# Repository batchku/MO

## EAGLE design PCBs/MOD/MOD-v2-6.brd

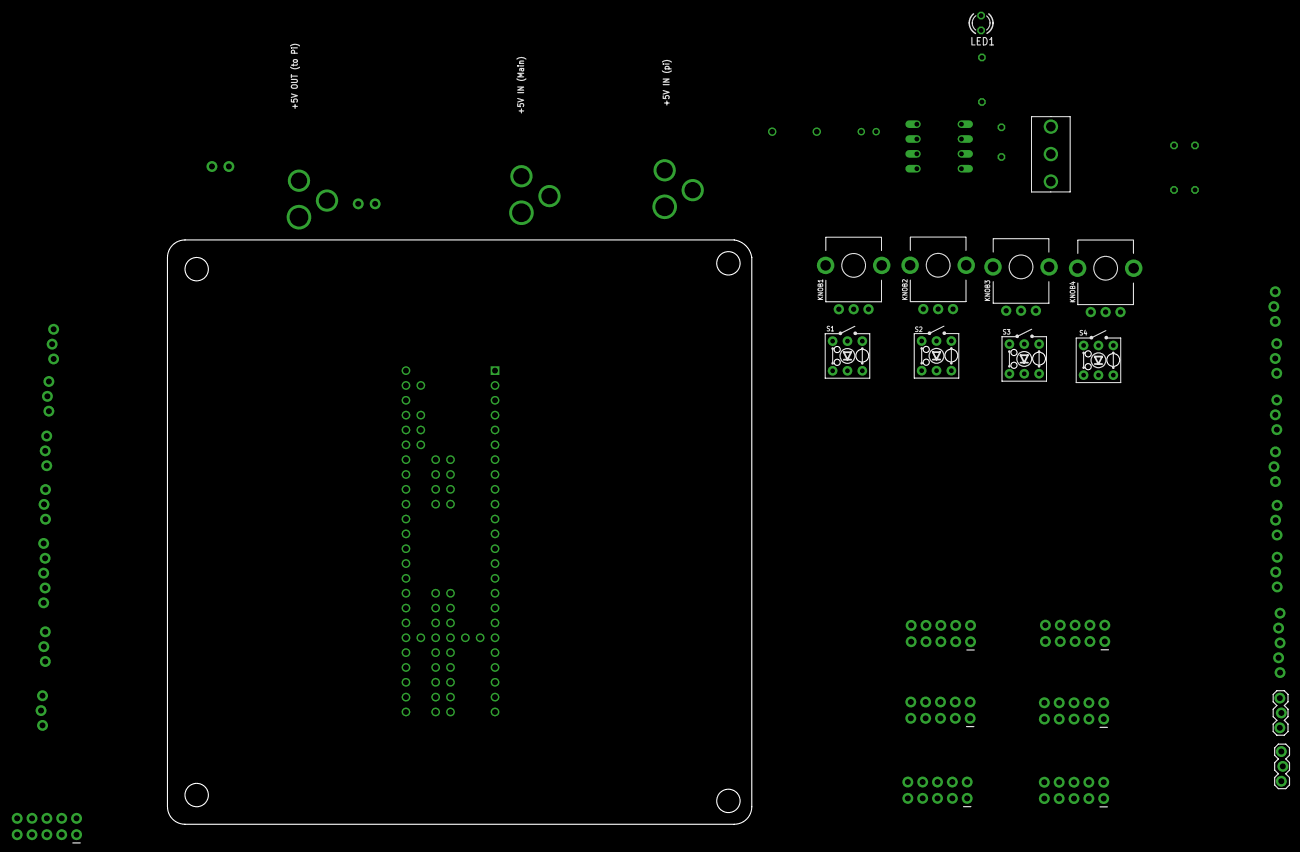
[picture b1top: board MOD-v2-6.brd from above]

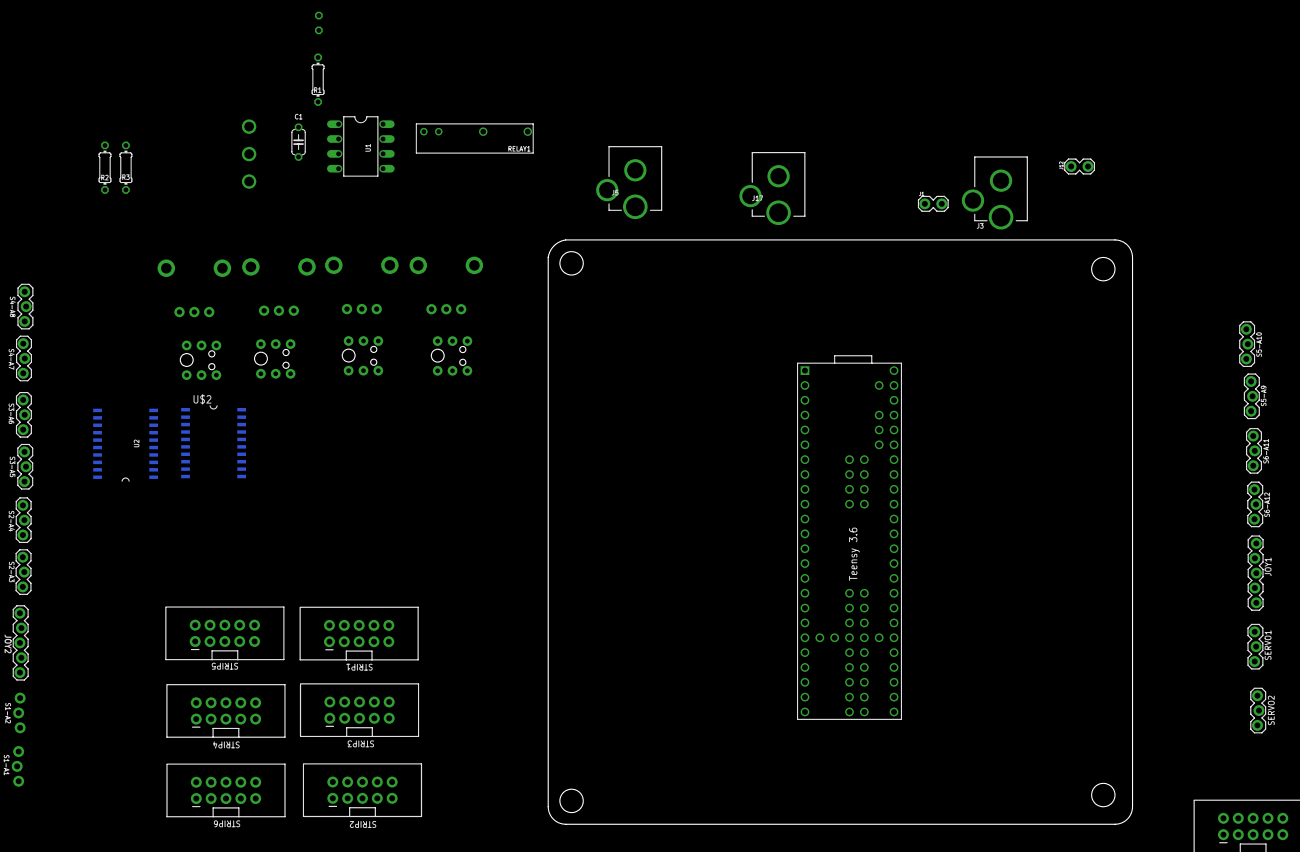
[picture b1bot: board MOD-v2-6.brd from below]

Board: 2 copper layers, 47 parts (35 on the bottom side), 92 nets, no tracks yet.

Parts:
C1: 10uF; C050-024X044
J1: Teensy-5V; 1X02_LOCK
J3: +5V OUT (to Pi); DCJACK_2MM_PTH
J4: ACTUATORS; 2X5-SHROUDED_LOCK
J5: +5V IN (Pi); DCJACK_2MM_PTH
J12: RPi-Shutdown; 1X02_LOCK
J17: +5V IN (Main); DCJACK_2MM_PTH
JOY1: JOY1; 1X05_LOCK
JOY2: JOY2; 1X05_LOCK
KNOB1, KNOB2, KNOB3, KNOB4: POT_ALPHA_RD901F-40-(L)R1
LED1: LED3MM
R1: 330; 0204/7
R2: 2.2K; 0204/7
R3: 3.3K; 0204/7
RELAY1: RELAY-OMRON-G6DN; G6DN-1A
S1, S2, S3, S4: SW-LEDPTH; SWITCH_TR2-MOMENTARY-LED
S1-A1, S3-A5, S5-A9: AN5; 1X03_LOCK
S1-A2, S3-A6, S5-A10: AN6; 1X03_LOCK
S2-A3, S4-A7, S6-A11: AN7; 1X03_LOCK
S2-A4, S4-A8, S6-A12: AN8; 1X03_LOCK
SERVO1: SERVO1; 1X03_LOCK@1
SERVO2: SERVO2; 1X03_LOCK@1
STRIP1, STRIP2, STRIP3, STRIP4, STRIP5, STRIP6: 2X5-SHROUDED_LOCK
SW2: 500SSP1S2M2QEA; SWITCH_SPDT_500SSP1S2M2QEA
TEENSY: TEENSY3_6-ALI_NO-USB-HOST; TEENSY3-6_NO-USB-HOST
U1: ATTINY85; DIL08
U2: A2982; SOIC20
U$2: A2982; SOIC20

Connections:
+3V3: J4.9, JOY1.1, JOY2.1, KNOB1.1, KNOB2.1, KNOB3.1, KNOB4.1, S1-A1.1, S1-A2.1, S2-A3.1, S2-A4.1, S3-A5.1, S3-A6.1, S4-A7.1, S4-A8.1, S5-A9.1, S5-A10.1, S6-A11.1, S6-A12.1, STRIP1.9, STRIP2.9, STRIP3.9, STRIP4.9, STRIP5.9, STRIP6.9, TEENSY.3V3(1), TEENSY.3V3(2), TEENSY.3V3(3), TEENSY.3V3(4)
+5V: C1.1, J1.2, J4.7, J4.8, J17.PWR, SERVO1.2, SERVO2.2, SW2.1, U1.8, U2.9, U$2.9
+5V-BATTERY-PI: J5.PWR, RELAY1.5
AGND: JOY1.2, JOY2.2, KNOB1.3, KNOB2.3, KNOB3.3, KNOB4.3, S1-A1.2, S1-A2.2, S2-A3.2, S2-A4.2, S3-A5.2, S3-A6.2, S4-A7.2, S4-A8.2, S5-A9.2, S5-A10.2, S6-A11.2, S6-A12.2, STRIP1.8, STRIP2.8, STRIP3.8, STRIP4.8, STRIP5.8, STRIP6.8, TEENSY.AGND
AN1: S1-A1.3, STRIP1.1, TEENSY.39
AN2: S1-A2.3, STRIP1.2, TEENSY.DAC0
AN3: S2-A3.3, STRIP2.1, TEENSY.DAC1
AN4: S2-A4.3, STRIP2.2, TEENSY.15
AN5: S3-A5.3, STRIP3.1, TEENSY.18
AN6: S3-A6.3, STRIP3.2, TEENSY.19
AN7: S4-A7.3, STRIP4.1, TEENSY.20
AN8: S4-A8.3, STRIP4.2, TEENSY.21
AN9: KNOB1.2, S5-A9.3, STRIP5.1, TEENSY.49
AN10: KNOB2.2, S5-A10.3, STRIP5.2, TEENSY.50
AN11: KNOB3.2, S6-A11.3, STRIP6.1, TEENSY.22
AN12: KNOB4.2, S6-A12.3, STRIP6.2, TEENSY.23
BTN1: STRIP1.3, TEENSY.48
BTN2: STRIP1.4, TEENSY.51
BTN3: STRIP2.3, TEENSY.42
BTN4: STRIP2.4, TEENSY.52
BTN5: STRIP3.3, TEENSY.40
BTN6: STRIP3.4, TEENSY.28
BTN7: STRIP4.3, TEENSY.27
BTN8: STRIP4.4, TEENSY.26
BTN9: STRIP5.3, TEENSY.25
BTN10: STRIP5.4, TEENSY.24
BTN11: STRIP6.3, TEENSY.12
BTN12: STRIP6.4, TEENSY.11
BTN13: S1.3, TEENSY.13
BTN14: S2.3, TEENSY.54
BTN15: S3.3, TEENSY.56
BTN16: S4.3, TEENSY.1
GND: C1.2, J3.GND, J4.10, J5.GND, J12.2, J17.GND, LED1.K, R3.2, RELAY1.2, S1.1, S1.C, S2.1, S2.C, S3.1, S3.C, S4.1, S4.C, SERVO1.1, SERVO2.1, STRIP1.10, STRIP2.10, STRIP3.10, STRIP4.10, STRIP5.10, STRIP6.10, SW2.3, TEENSY.G0, TEENSY.G1, TEENSY.G2, TEENSY.G3, TEENSY.G6, U1.4, U2.11, U2.12, U$2.11, U$2.12
GNDBREAK: J3.GNDBREAK, J5.GNDBREAK, J17.GNDBREAK
JOYB1: JOY1.5, TEENSY.47
JOYB2: JOY2.5, TEENSY.44
JOYH1: JOY1.3, TEENSY.A11
JOYH2: JOY2.3, TEENSY.31
JOYV1: JOY1.4, TEENSY.A10
JOYV2: JOY2.4, TEENSY.32
LED1: STRIP1.7, TEENSY.43
LED2: STRIP2.7, TEENSY.41
LED3: STRIP3.7, TEENSY.53
LED4: STRIP4.7, TEENSY.0
LED5: STRIP5.7, TEENSY.55
LED6: STRIP6.7, TEENSY.57
M_INA: J4.2, TEENSY.45
M_INB: J4.4, TEENSY.46
M_PWMA: J4.1, TEENSY.36
M_PWMB: J4.3, TEENSY.35
unnamed: LED1.A, R1.2
unnamed: J12.1, R2.2, R3.1
unnamed: J1.1, TEENSY.VIN
PI-REST: R2.1, U1.6
PWM1: TEENSY.2, U2.8
PWM2: TEENSY.3, U2.7
PWM3: TEENSY.4, U2.6
PWM4: TEENSY.5, U2.5
PWM5: TEENSY.6, U2.4
PWM6: TEENSY.7, U2.3
PWM7: TEENSY.8, U2.2
PWM8: TEENSY.9, U2.1
PWM9: TEENSY.37, U$2.8
PWM10: TEENSY.29, U$2.7
PWM11: TEENSY.38, U$2.6
PWM12: TEENSY.14, U$2.5
PWM13: TEENSY.30, U$2.4
PWM14: TEENSY.16, U$2.3
PWM15: TEENSY.10, U$2.2
PWM16: TEENSY.17, U$2.1
PWM_1: STRIP1.5, U2.13
PWM_2: STRIP1.6, U2.14
PWM_3: STRIP2.5, U2.15
PWM_4: STRIP2.6, U2.16
PWM_5: STRIP3.5, U2.17
PWM_6: STRIP3.6, U2.18
PWM_7: STRIP4.5, U2.19
PWM_8: STRIP4.6, U2.20
PWM_9: STRIP5.5, U$2.13
PWM_10: STRIP5.6, U$2.14
PWM_11: STRIP6.5, U$2.15
PWM_12: STRIP6.6, U$2.16
PWM_13: S1.A, U$2.17
PWM_14: S2.A, U$2.18
PWM_15: S3.A, U$2.19
PWM_16: S4.A, U$2.20
RELAY-PWR: J3.PWR, RELAY1.8
S1: J4.5, SERVO1.3, TEENSY.33
S2: J4.6, SERVO2.3, TEENSY.34
TINY_LED: R1.1, U1.3
TINY_RELAY: RELAY1.1, U1.7
TINY_SWITCH: SW2.2, U1.5

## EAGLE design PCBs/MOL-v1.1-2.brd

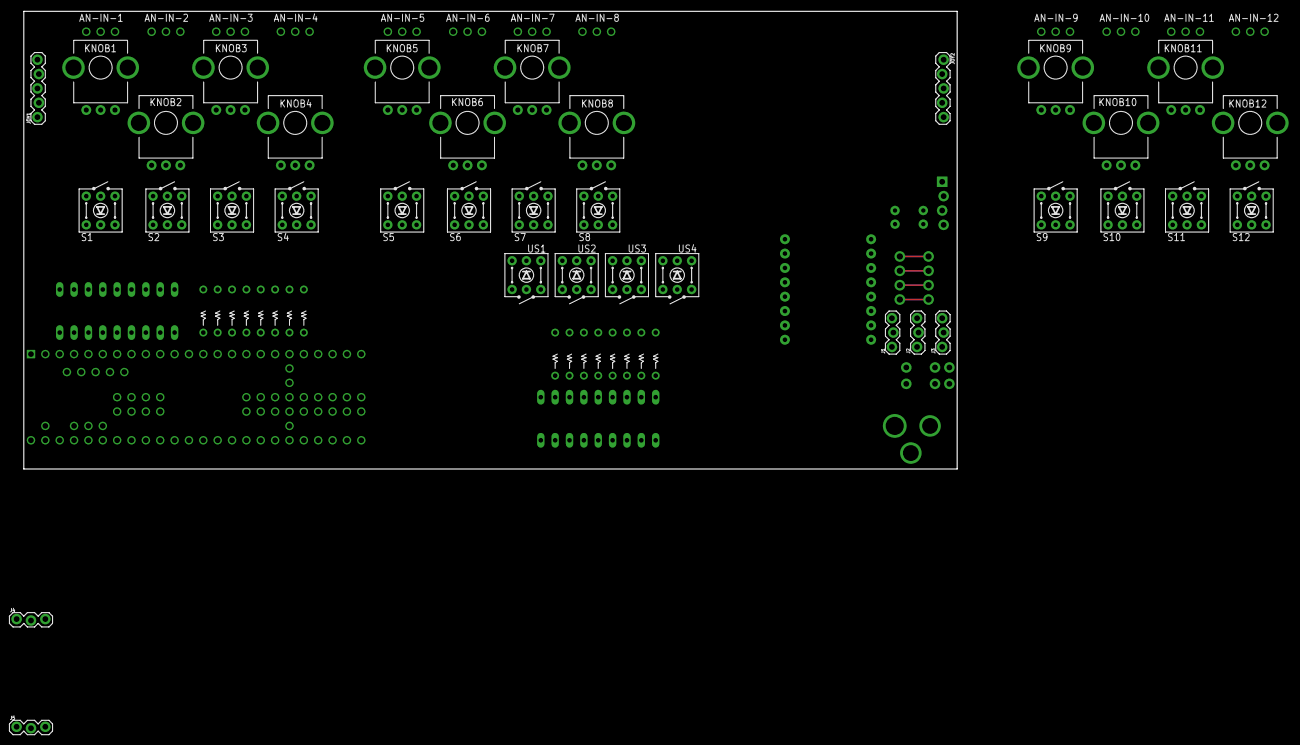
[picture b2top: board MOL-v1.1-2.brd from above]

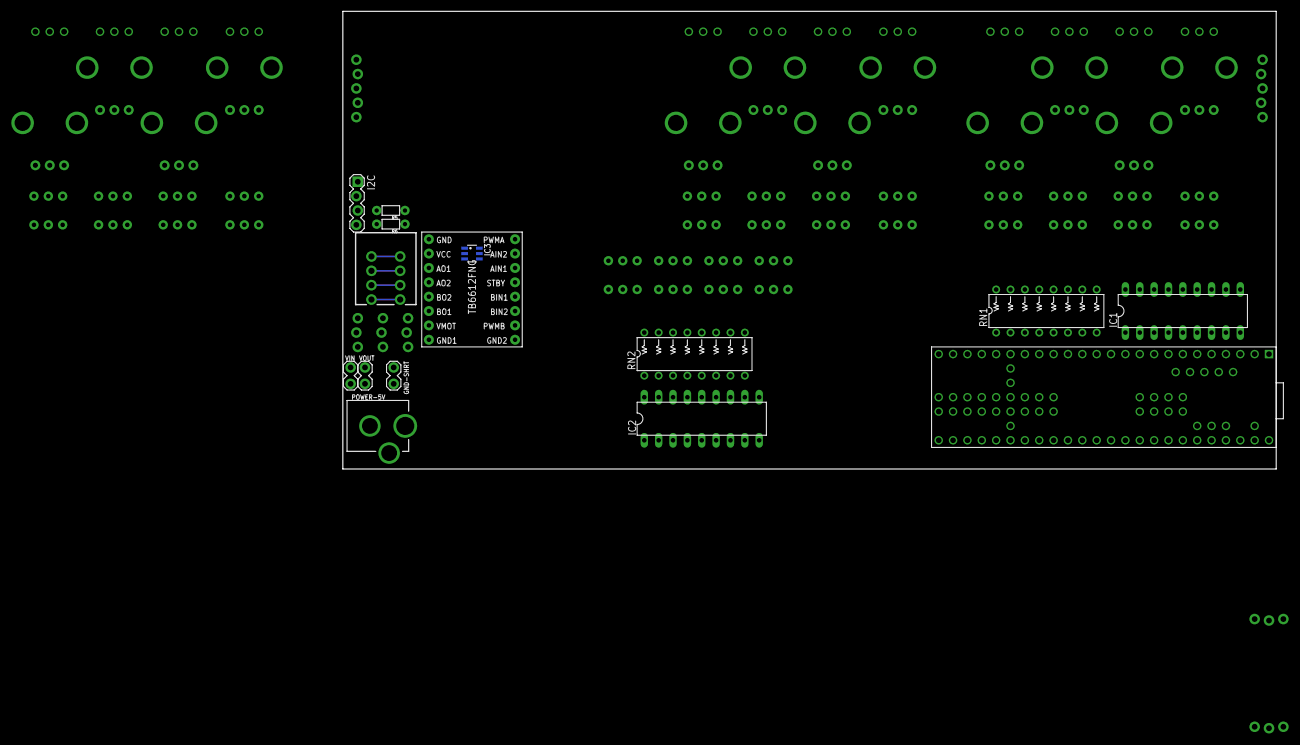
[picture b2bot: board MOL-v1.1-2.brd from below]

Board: 2 copper layers, 165.1 x 81.0 mm, 62 parts (15 on the bottom side), 80 nets, no tracks yet.

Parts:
AN-IN-1, AN-IN-2, AN-IN-3, AN-IN-4, AN-IN-5, AN-IN-6, AN-IN-7, AN-IN-8, AN-IN-9, AN-IN-10, AN-IN-11, AN-IN-12: 1X03_NO_SILK
GND-SHRT: 1X02_LOCK
I2C: 1X04_LOCK
IC1, IC2: ULN2803; DIL18
IC3: SN74LVC2G04DBV; SOT23-6
J1, J4: SERVO 1; 1X03_LOCK@1
J2, J5: SERVO 2; 1X03_LOCK@1
J3: SERVO 3; 1X03_LOCK@1
JOY1, JOY2: 1X05_LOCK
KNOB1, KNOB2, KNOB3, KNOB4, KNOB5, KNOB6, KNOB7, KNOB8, KNOB9, KNOB10, KNOB11, KNOB12: TRIM-PCB-9MM
MOTORS1: SPRINGTERMINAL-2.54MM-4
POWER-5V: DCJACK_2MM_PTH
R5, R6: 1/6W-RES
RN1, RN2: 330; RESISTOR-NET-8P-DIL16
S1, S2, S3, S4, S5, S6, S7, S8, S9, S10, S11, S12: SW-LEDPTH; TR2-SWITCH-MOMENTARY-LED
TEENSY: TEENSY3_6--ALLPINS; T36
U$7: POLOLU_TB6612FNG
US1, US2, US3, US4: SW-LEDPTH; TR2-SWITCH-MOMENTARY-LED
VIN: 1X02_LOCK
VOUT: 1X02_LOCK

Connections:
+3V3: AN-IN-1.1, AN-IN-2.1, AN-IN-3.1, AN-IN-4.1, AN-IN-5.1, AN-IN-6.1, AN-IN-7.1, AN-IN-8.1, AN-IN-9.1, AN-IN-10.1, AN-IN-11.1, AN-IN-12.1, I2C.1, IC3.5, JOY1.2, JOY2.2, KNOB1.1, KNOB2.1, KNOB3.1, KNOB4.1, KNOB5.1, KNOB6.1, KNOB7.1, KNOB8.1, KNOB9.1, KNOB10.1, KNOB11.1, KNOB12.1, R5.1, R6.1, TEENSY.3V3(1), TEENSY.3V3(2), TEENSY.3V3(3), TEENSY.3V3(4), U$7.STBY, U$7.VCC
+5V: IC1.10, IC2.10, J1.2, J2.2, J3.2, J4.2, J5.2, POWER-5V.PWR, VIN.1
AGND: AN-IN-1.3, AN-IN-2.3, AN-IN-3.3, AN-IN-4.3, AN-IN-5.3, AN-IN-6.3, AN-IN-7.3, AN-IN-8.3, AN-IN-9.3, AN-IN-10.3, AN-IN-11.3, AN-IN-12.3, JOY1.1, JOY2.1, KNOB1.3, KNOB2.3, KNOB3.3, KNOB4.3, KNOB5.3, KNOB6.3, KNOB7.3, KNOB8.3, KNOB9.3, KNOB10.3, KNOB11.3, KNOB12.3, TEENSY.AGND
AN1: AN-IN-1.2, AN-IN-5.2, AN-IN-9.2, KNOB1.2, KNOB5.2, KNOB9.2, TEENSY.14
AN2: AN-IN-2.2, AN-IN-6.2, AN-IN-10.2, KNOB2.2, KNOB6.2, KNOB10.2, TEENSY.15
AN3: AN-IN-3.2, AN-IN-7.2, AN-IN-11.2, KNOB3.2, KNOB7.2, KNOB11.2, TEENSY.16
AN4: AN-IN-4.2, AN-IN-8.2, AN-IN-12.2, KNOB4.2, KNOB8.2, KNOB12.2, TEENSY.33
B1: S1.1, S5.1, S9.1, TEENSY.11
B2: S2.1, S6.1, S10.1, TEENSY.12
B3: S3.1, S7.1, S11.1, TEENSY.24
B4: S4.1, S8.1, S12.1, TEENSY.25
GND: GND-SHRT.2, I2C.2, IC1.9, IC2.9, IC3.2, J1.1, J2.1, J3.1, J4.1, J5.1, S1.3, S2.3, S3.3, S4.3, S5.3, S6.3, S7.3, S8.3, S9.3, S10.3, S11.3, S12.3, TEENSY.G0, TEENSY.G1, TEENSY.G2, TEENSY.G3, TEENSY.G4, TEENSY.G5, TEENSY.G6, U$7.GND, US1.3, US2.3, US3.3, US4.3, VIN.2, VOUT.2
GND_MOT: GND-SHRT.1, POWER-5V.GND, U$7.GND1, U$7.GND2
I2C_SCL: I2C.3, R5.2
I2C_SDA: I2C.4, R6.2
JOYB1: JOY1.5, TEENSY.1
JOYB2: JOY2.5, TEENSY.0
JOYH1: JOY1.3, TEENSY.20
JOYH2: JOY2.3, TEENSY.18
JOYV1: JOY1.4, TEENSY.19
JOYV2: JOY2.4, TEENSY.17
L1: IC1.8, TEENSY.2
L2: IC1.7, TEENSY.3
L3: IC1.6, TEENSY.4
L4: IC1.5, TEENSY.5
L5: IC1.4, TEENSY.6
L6: IC1.3, TEENSY.7
L7: IC1.2, TEENSY.8
L8: IC1.1, TEENSY.23
L9: IC2.8, TEENSY.29
L10: IC2.7, TEENSY.30
L11: IC2.6, TEENSY.31
L12: IC2.5, TEENSY.32
LED1: RN1.H2, S1.C, S5.C, S9.C
LED2: RN1.G2, S2.C, S6.C, S10.C
LED3: RN1.F2, S3.C, S7.C, S11.C
LED4: RN1.E2, S4.C, S8.C, S12.C
M_AIN: IC3.3, TEENSY.40, U$7.AIN1
M_BIN: IC3.1, TEENSY.41, U$7.BIN2
M_PWMA: TEENSY.21, U$7.PWMA
M_PWMB: TEENSY.22, U$7.PWMB
unnamed: IC3.6, U$7.BIN1
unnamed: IC3.4, U$7.AIN2
unnamed: IC1.18, RN1.A1
unnamed: IC1.17, RN1.B1
unnamed: IC1.16, RN1.C1
unnamed: IC1.15, RN1.D1
unnamed: IC1.14, RN1.E1
unnamed: IC1.13, RN1.F1
unnamed: IC1.12, RN1.G1
unnamed: IC1.11, RN1.H1
unnamed: IC2.18, RN2.A1
unnamed: IC2.17, RN2.B1
unnamed: IC2.16, RN2.C1
unnamed: IC2.15, RN2.D1
unnamed: IC2.14, RN2.E1
unnamed: IC2.12, RN2.G1
unnamed: IC2.11, RN2.H1
unnamed: IC2.13, RN2.F1
unnamed: MOTORS1.P$1, U$7.BO1
unnamed: MOTORS1.P$2, U$7.BO2
unnamed: MOTORS1.P$3, U$7.AO2
unnamed: MOTORS1.P$4, U$7.AO1
S1: J1.3, J4.3, TEENSY.9
S2: J2.3, J5.3, TEENSY.10
S3: J3.3, TEENSY.49
UB1: TEENSY.57, US1.1
UB2: TEENSY.56, US2.1
UB3: TEENSY.55, US3.1
UB4: TEENSY.54, US4.1
UL1: IC2.4, TEENSY.53
UL2: IC2.3, TEENSY.52
UL3: IC2.2, TEENSY.51
UL4: IC2.1, TEENSY.50
ULED1: RN2.D2, US1.C
ULED2: RN2.C2, US2.C
ULED3: RN2.B2, US3.C
ULED4: RN2.A2, US4.C
V+: S1.A, S2.A, S3.A, S4.A, S5.A, S6.A, S7.A, S8.A, S9.A, S10.A, S11.A, S12.A, US1.A, US2.A, US3.A, US4.A
VMOT: U$7.VMOT, VOUT.1

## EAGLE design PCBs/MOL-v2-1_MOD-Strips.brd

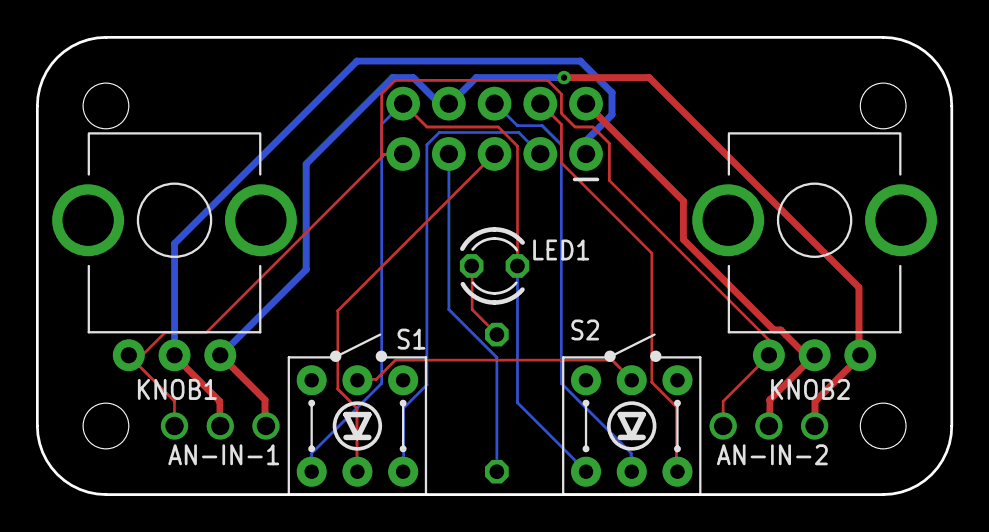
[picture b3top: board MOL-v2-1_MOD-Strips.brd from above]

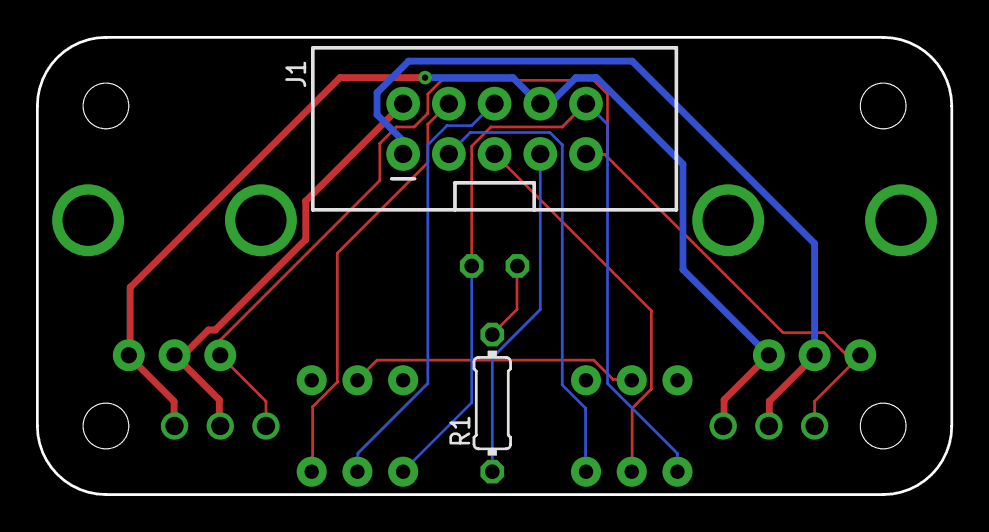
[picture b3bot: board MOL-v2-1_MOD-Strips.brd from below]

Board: 2 copper layers, 50.8 x 25.4 mm, 9 parts (2 on the bottom side), 12 nets.

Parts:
AN-IN-1, AN-IN-2: 1X03_NO_SILK
J1: 2X5-SHROUDED_LOCK
KNOB1, KNOB2: TRIM-PCB-9MM
LED1: LED3MM
R1: 220; 0204/7
S1, S2: SW-LEDPTH; TR2-SWITCH-MOMENTARY-LED

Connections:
+3V3: AN-IN-1.1, AN-IN-2.1, J1.9, KNOB1.1, KNOB2.1
AGND: AN-IN-1.3, AN-IN-2.3, J1.8, KNOB1.3, KNOB2.3
AN1: AN-IN-1.2, J1.1, KNOB1.2
AN2: AN-IN-2.2, J1.2, KNOB2.2
B1: J1.3, S1.1
B2: J1.4, S2.1
GND: J1.10, LED1.K, S1.3, S2.3
LED1: J1.7, R1.1
N1: LED1.A, R1.2
PWM_1: J1.5, S1.C
PWM_2: J1.6, S2.C
V+: S1.A, S2.A

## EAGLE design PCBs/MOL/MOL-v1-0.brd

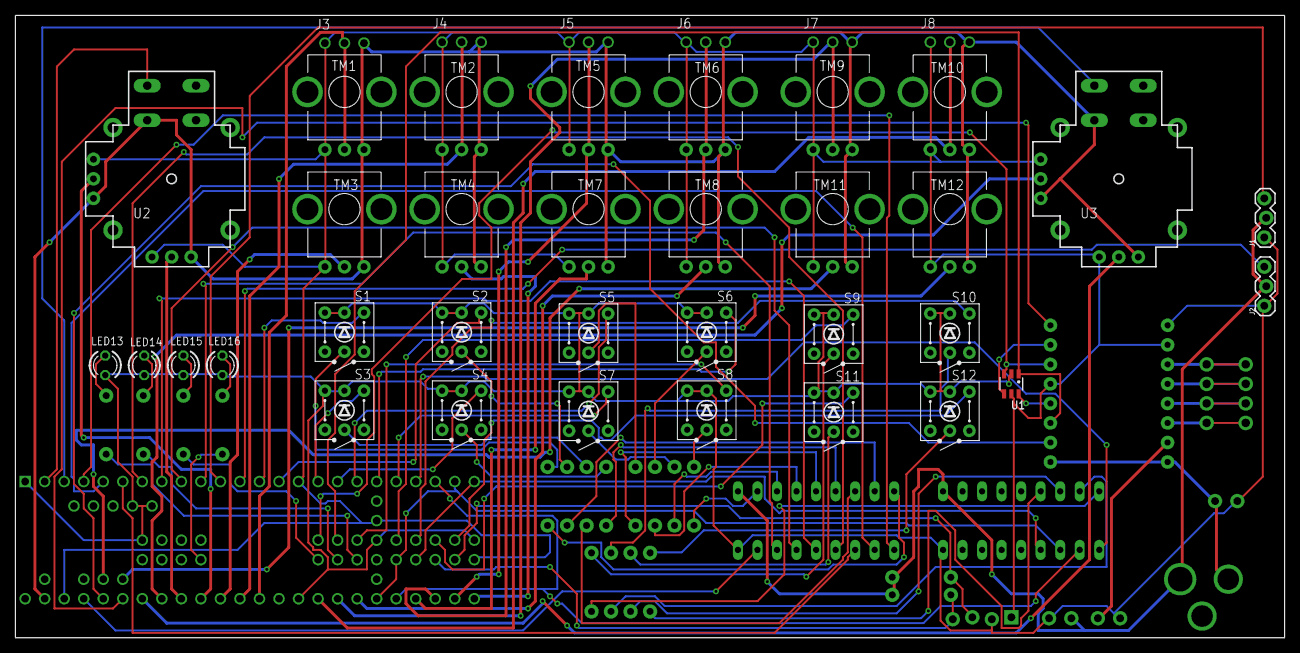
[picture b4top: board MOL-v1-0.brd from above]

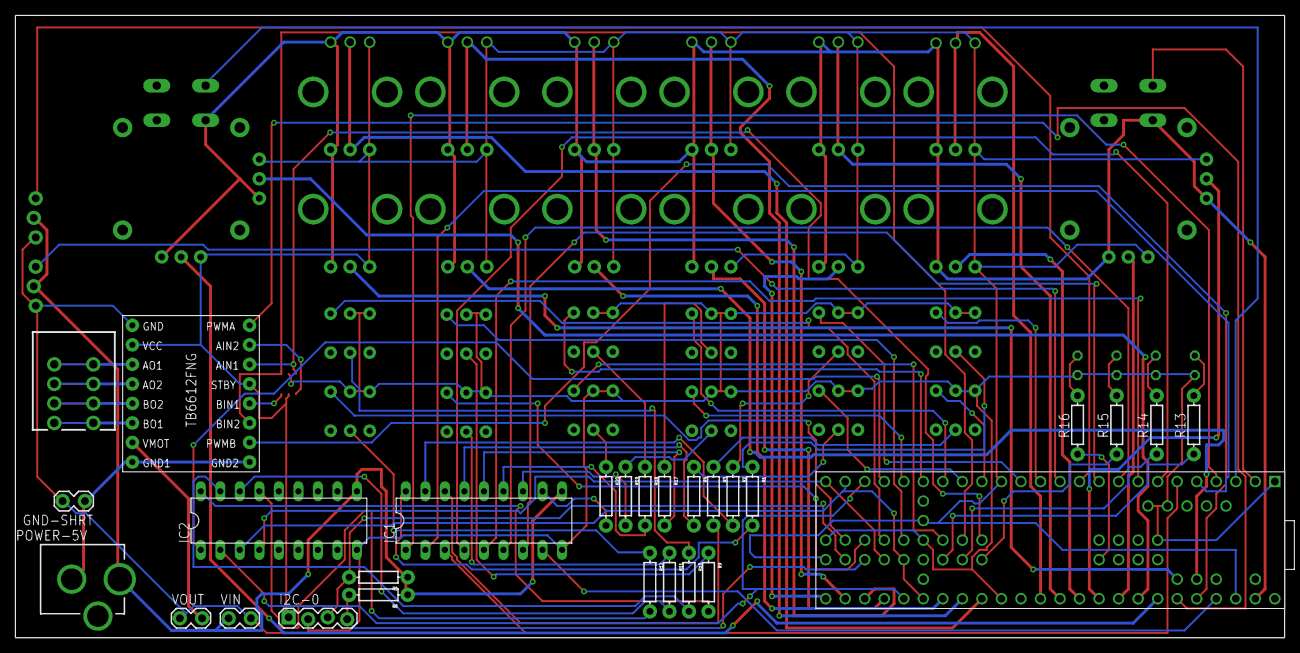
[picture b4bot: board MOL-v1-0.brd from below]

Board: 2 copper layers, 165.1 x 81.0 mm, 67 parts (28 on the bottom side), 94 nets.

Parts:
GND-SHRT: 1X02_LOCK
I2C-0: 1X04_LOCK
IC1, IC2: ULN2803; DIL18
J1: SERVO 1; 1X03_LOCK@1
J2: SERVO 2; 1X03_LOCK@1
J3, J4, J5, J6, J7, J8: 1X03_NO_SILK
LED13, LED14, LED15, LED16: LED3MM
MOTORS1: SPRINGTERMINAL-2.54MM-4
POWER-5V: DCJACK_2MM_PTH
R1, R2, R3, R4, R5, R6, R9, R10, R11, R12, R13, R14, R15, R16, R17, R18, R19, R20: AXIAL-0.3EZ
S1, S2, S3, S4, S5, S6, S7, S8, S9, S10, S11, S12: SW-LEDPTH; TR2-SWITCH-MOMENTARY-LED
TM1, TM2, TM3, TM4, TM5, TM6, TM7, TM8, TM9, TM10, TM11, TM12: TRIM-PCB-9MM
U1: SN74LVC2G04DBV; SOT23-6
U2, U3: JOYSTICKPTH; JOYSTICK
U$1: TEENSY3_6--ALLPINS; T36
U$7: POLOLU_TB6612FNG
VIN: 1X02_LOCK
VOUT: 1X02_LOCK

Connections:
+3V3: I2C-0.1, J3.1, J4.1, J5.1, J6.1, J7.1, J8.1, TM1.1, TM2.1, TM3.1, TM4.1, TM5.1, TM6.1, TM7.1, TM8.1, TM9.1, TM10.1, TM11.1, TM12.1, U1.5, U2.H1, U2.V1, U3.H1, U3.V1, U$1.3V3(1), U$1.3V3(2), U$1.3V3(3), U$1.3V3(4), U$7.STBY, U$7.VCC
+5V: IC1.10, IC2.10, J1.2, J2.2, POWER-5V.PWR, R5.P$1, R6.P$1, VIN.1
A1: J3.2, TM1.2, U$1.14
A2: J4.2, TM2.2, U$1.15
A3: TM3.2, U$1.16
A4: TM4.2, U$1.33
A5: J5.2, TM5.2, U$1.34
A6: J6.2, TM6.2, U$1.35
A7: TM7.2, U$1.36
A8: TM8.2, U$1.39
A9: J7.2, TM9.2, U$1.DAC0
A10: J8.2, TM10.2, U$1.DAC1
A11: TM11.2, U$1.A10
A12: TM12.2, U$1.A11
AGND: J3.3, J4.3, J5.3, J6.3, J7.3, J8.3, TM1.3, TM2.3, TM3.3, TM4.3, TM5.3, TM6.3, TM7.3, TM8.3, TM9.3, TM10.3, TM11.3, TM12.3, U2.B2A, U2.H3, U2.V3, U3.B2A, U3.H3, U3.V3, U$1.AGND
B1: S1.3, U$1.11
B2: S2.3, U$1.12
B3: S3.3, U$1.24
B4: S4.3, U$1.25
B5: S5.3, U$1.26
B6: S6.3, U$1.27
B7: S7.3, U$1.28
B8: S8.3, U$1.42
B9: S9.3, U$1.43
B10: S10.3, U$1.44
B11: S11.3, U$1.45
B12: S12.3, U$1.46
GND: GND-SHRT.2, I2C-0.2, IC1.9, IC2.9, J1.1, J2.1, LED13.K, LED14.K, LED15.K, LED16.K, S1.1, S1.C, S2.1, S2.C, S3.1, S3.C, S4.1, S4.C, S5.1, S5.C, S6.1, S6.C, S7.1, S7.C, S8.1, S8.C, S9.1, S9.C, S10.1, S10.C, S11.1, S11.C, S12.1, S12.C, U1.2, U$1.G0, U$1.G1, U$1.G2, U$1.G3, U$1.G4, U$1.G5, U$1.G6, U$7.GND, VIN.2, VOUT.1
GND_MOT: GND-SHRT.1, POWER-5V.GND, U$7.GND1, U$7.GND2
I2C_SCL: I2C-0.3, R5.P$2, U$1.47
I2C_SDA: I2C-0.4, R6.P$2, U$1.48
L1: IC1.1, U$1.2
L2: IC1.2, U$1.3
L3: IC1.3, U$1.4
L4: IC1.4, U$1.5
L5: IC1.5, U$1.6
L6: IC1.6, U$1.7
L7: IC1.7, U$1.8
L8: IC1.8, U$1.23
L9: IC2.1, U$1.29
L10: IC2.2, U$1.30, U$1.37
L11: IC2.3, U$1.31, U$1.38, U$1.50
L12: IC2.4, U$1.32, U$1.49
LED1: IC1.18, R1.P$2
LED2: IC1.17, R2.P$2
LED3: IC1.16, R3.P$2
LED4: IC1.15, R4.P$2
LED5: IC1.14, R17.P$2
LED6: IC1.13, R18.P$2
LED7: IC1.12, R19.P$2
LED8: IC1.11, R20.P$2
LED9: IC2.18, R9.P$2
LED10: IC2.17, R10.P$2
LED11: IC2.16, R11.P$2
LED12: IC2.15, R12.P$2
M_AIN: U1.3, U$1.40, U$7.AIN1
M_BIN: U1.1, U$1.41, U$7.BIN2
M_JOYB: U2.B1A, U$1.0
M_JOYH: U2.H2, U$1.18
M_JOYV: U2.V2, U$1.17
M_PWMA: U$1.21, U$7.PWMA
M_PWMB: U$1.22, U$7.PWMB
unnamed: R1.P$1, S1.A
unnamed: LED13.A, R13.P$1
unnamed: LED14.A, R14.P$1
unnamed: LED15.A, R15.P$1
unnamed: U1.6, U$7.BIN1
unnamed: U1.4, U$7.AIN2
unnamed: LED16.A, R16.P$1
unnamed: R2.P$1, S2.A
unnamed: R3.P$1, S3.A
unnamed: R4.P$1, S4.A
unnamed: R9.P$1, S9.A
unnamed: R10.P$1, S10.A
unnamed: R11.P$1, S11.A
unnamed: R12.P$1, S12.A
unnamed: R17.P$1, S5.A
unnamed: R18.P$1, S6.A
unnamed: R19.P$1, S7.A
unnamed: R20.P$1, S8.A
unnamed: MOTORS1.P$1, U$7.BO1
unnamed: MOTORS1.P$2, U$7.BO2
unnamed: MOTORS1.P$3, U$7.AO2
unnamed: MOTORS1.P$4, U$7.AO1
S1: J1.3, U$1.9
S2: J2.3, U$1.10
S_JOYB: U3.B1A, U$1.1
S_JOYH: U3.H2, U$1.20
S_JOYV: U3.V2, U$1.19
U1: R13.P$2, U$1.51
U2: R14.P$2, U$1.52
U3: R15.P$2, U$1.53
U4: R16.P$2, U$1.54
VMOT: U$7.VMOT, VOUT.2

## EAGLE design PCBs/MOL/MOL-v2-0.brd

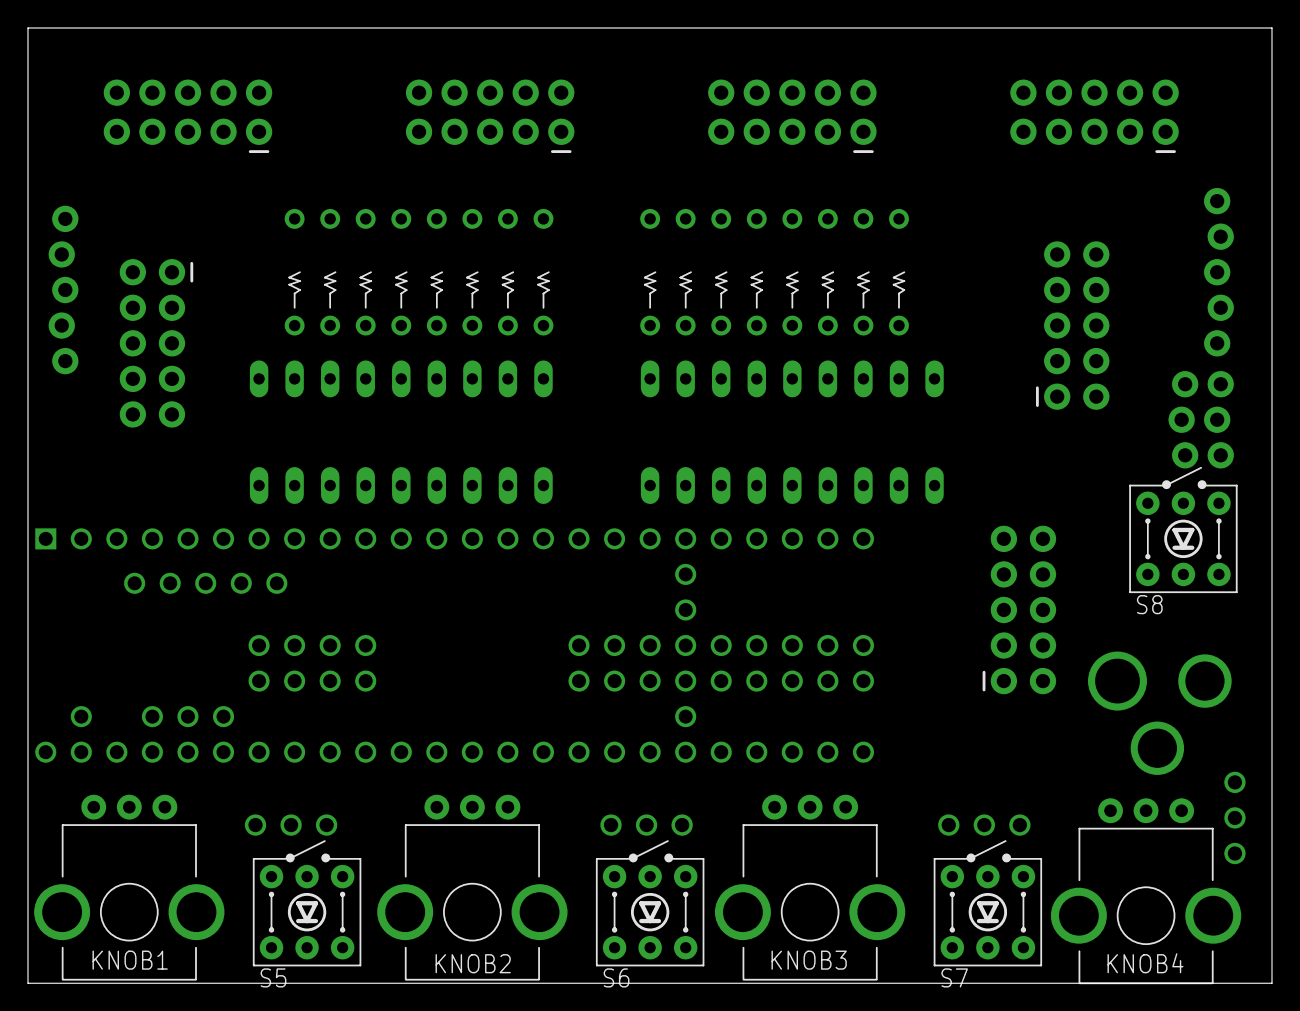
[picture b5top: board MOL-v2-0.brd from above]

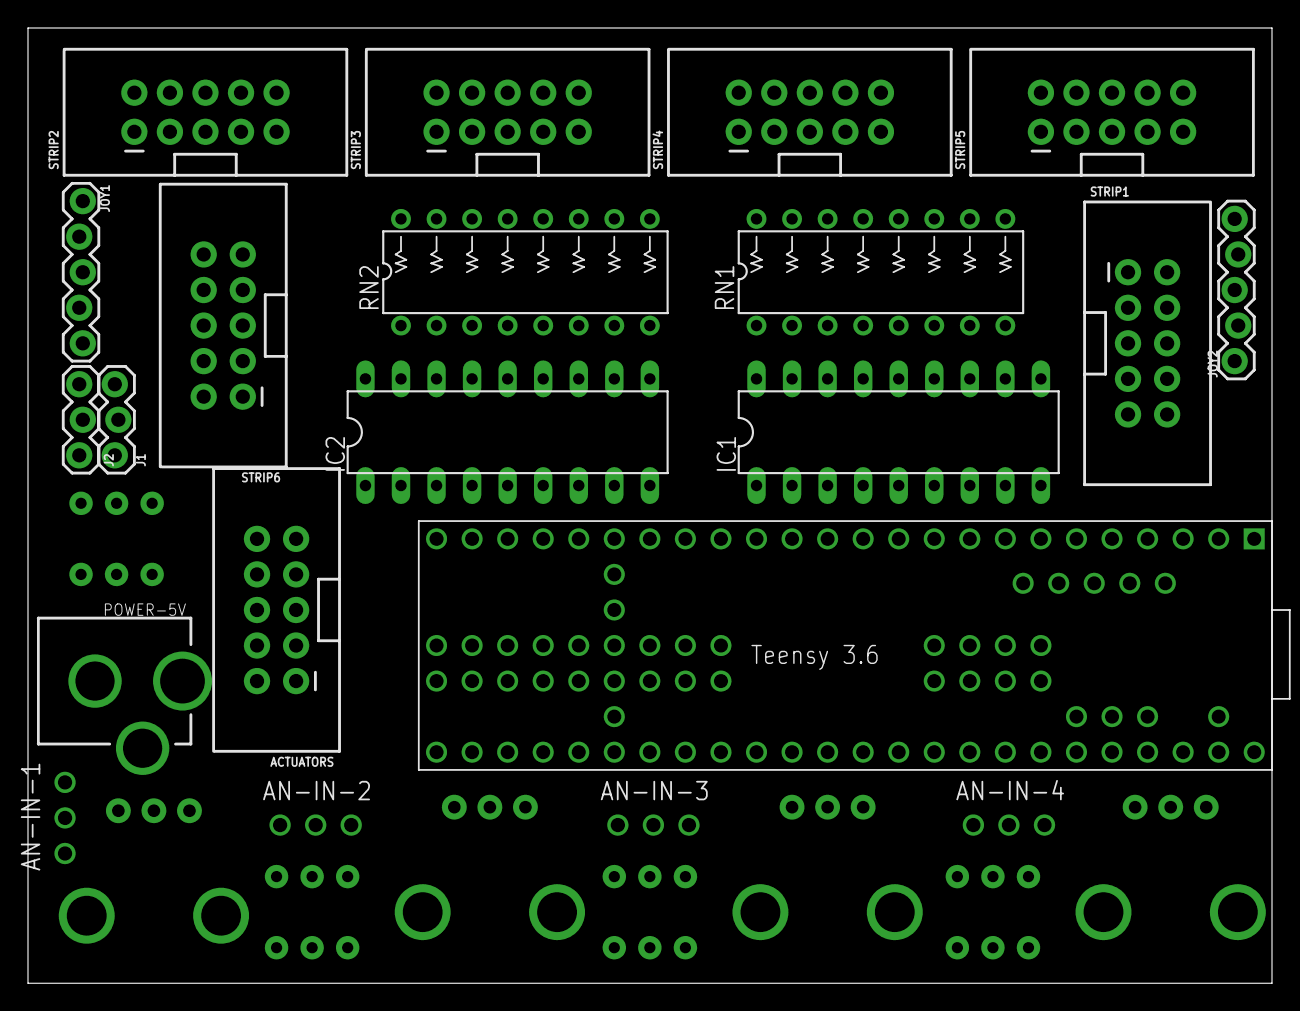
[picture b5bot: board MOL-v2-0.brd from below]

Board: 2 copper layers, 88.9 x 68.2 mm, 29 parts (21 on the bottom side), 95 nets, no tracks yet.

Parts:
ACTUATORS: 2X5-SHROUDED_LOCK
AN-IN-1, AN-IN-2, AN-IN-3, AN-IN-4: 1X03_NO_SILK
IC1, IC2: ULN2803; DIL18
J1: Servo1; 1X03_LOCK@1
J2: Servo2; 1X03_LOCK@1
JOY1, JOY2: 1X05_LOCK
KNOB1, KNOB2, KNOB3, KNOB4: TRIM-PCB-9MM
POWER-5V: DCJACK_2MM_PTH
RN1, RN2: 330; RESISTOR-NET-8P-DIL16
S5, S6, S7, S8: SW-LEDPTH; TR2-SWITCH-MOMENTARY-LED
STRIP1, STRIP2, STRIP3, STRIP4, STRIP5, STRIP6: 2X5-SHROUDED_LOCK
U$2: TEENSY3_6--ALLPINS; T36

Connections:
+3V3: ACTUATORS.9, AN-IN-1.1, AN-IN-2.1, AN-IN-3.1, AN-IN-4.1, JOY1.2, JOY2.2, KNOB1.1, KNOB2.1, KNOB3.1, KNOB4.1, STRIP1.9, STRIP2.9, STRIP3.9, STRIP4.9, STRIP5.9, STRIP6.9, U$2.3V3(1), U$2.3V3(2), U$2.3V3(3), U$2.3V3(4)
+5V: ACTUATORS.7, ACTUATORS.8, IC1.10, IC2.10, J1.2, J2.2, POWER-5V.PWR
AGND: AN-IN-1.3, AN-IN-2.3, AN-IN-3.3, AN-IN-4.3, JOY1.1, JOY2.1, KNOB1.3, KNOB2.3, KNOB3.3, KNOB4.3, STRIP1.8, STRIP2.8, STRIP3.8, STRIP4.8, STRIP5.8, STRIP6.8, U$2.AGND
AN1: STRIP1.1, U$2.15
AN2: STRIP1.2, U$2.16
AN3: STRIP2.1, U$2.14
AN4: STRIP2.2, U$2.33
AN5: AN-IN-1.2, STRIP3.1, U$2.34
AN6: AN-IN-2.2, STRIP3.2, U$2.35
AN7: AN-IN-3.2, STRIP4.1, U$2.39
AN8: AN-IN-4.2, STRIP4.2, U$2.36
AN9: KNOB1.2, STRIP5.1, U$2.DAC0
AN10: KNOB2.2, STRIP5.2, U$2.DAC1
AN11: KNOB3.2, STRIP6.1, U$2.A10
AN12: KNOB4.2, STRIP6.2, U$2.A11
B1: STRIP1.3, U$2.12
B2: STRIP1.4, U$2.11
B3: STRIP2.3, U$2.28
B4: STRIP2.4, U$2.27
B5: STRIP3.3, U$2.26
B6: STRIP3.4, U$2.25
B7: STRIP4.3, U$2.24
B8: STRIP4.4, U$2.42
B9: STRIP5.3, U$2.43
B10: STRIP5.4, U$2.44
B11: STRIP6.3, U$2.45
B12: STRIP6.4, U$2.46
B13: S5.1, U$2.52
B14: S6.1, U$2.51
B15: S7.1, U$2.53
B16: S8.1, U$2.54
GND: ACTUATORS.10, IC1.9, IC2.9, J1.1, J2.1, POWER-5V.GND, S5.3, S6.3, S7.3, S8.3, STRIP1.10, STRIP2.10, STRIP3.10, STRIP4.10, STRIP5.10, STRIP6.10, U$2.G0, U$2.G1, U$2.G2, U$2.G3, U$2.G4, U$2.G5, U$2.G6
JOYB1: JOY1.5, U$2.1
JOYB2: JOY2.5, U$2.0
JOYH1: JOY1.3, U$2.20
JOYH2: JOY2.3, U$2.18
JOYV1: JOY1.4, U$2.19
JOYV2: JOY2.4, U$2.17
LED1: STRIP1.7, U$2.47
LED2: STRIP2.7, U$2.48
LED3: STRIP3.7, U$2.55
LED4: STRIP4.7, U$2.56
LED5: STRIP5.7, U$2.57
LED6: STRIP6.7, U$2.13
M_AIN: ACTUATORS.2, U$2.40
M_BIN: ACTUATORS.4, U$2.41
M_PWMA: ACTUATORS.1, U$2.29
M_PWMB: ACTUATORS.3, U$2.30
unnamed: IC1.18, RN1.A1
unnamed: IC1.17, RN1.B1
unnamed: IC1.16, RN1.C1
unnamed: IC1.15, RN1.D1
unnamed: IC1.14, RN1.E1
unnamed: IC1.13, RN1.F1
unnamed: IC1.12, RN1.G1
unnamed: IC1.11, RN1.H1
unnamed: IC2.18, RN2.A1
unnamed: IC2.17, RN2.B1
unnamed: IC2.16, RN2.C1
unnamed: IC2.15, RN2.D1
unnamed: IC2.14, RN2.E1
unnamed: IC2.12, RN2.G1
unnamed: IC2.11, RN2.H1
unnamed: IC2.13, RN2.F1
PWM1: IC1.8, U$2.2
PWM2: IC1.7, U$2.3
PWM3: IC1.6, U$2.4
PWM4: IC1.5, U$2.5
PWM5: IC1.4, U$2.6
PWM6: IC1.3, U$2.7
PWM7: IC1.2, U$2.8
PWM8: IC1.1, U$2.23
PWM9: IC2.8, U$2.21
PWM10: IC2.7, U$2.22
PWM11: IC2.6, U$2.31
PWM12: IC2.5, U$2.32
PWM_1: RN1.H2, STRIP1.5
PWM_2: RN1.G2, STRIP1.6
PWM_3: RN1.F2, STRIP2.5
PWM_4: RN1.E2, STRIP2.6
PWM_5: RN1.D2, STRIP3.5
PWM_6: RN1.C2, STRIP3.6
PWM_7: RN1.B2, STRIP4.5
PWM_8: RN1.A2, STRIP4.6
PWM_9: RN2.H2, STRIP5.5
PWM_10: RN2.G2, STRIP5.6
PWM_11: RN2.F2, STRIP6.5
PWM_12: RN2.E2, STRIP6.6
PWM_13: RN2.D2, S5.C, U$2.37
PWM_14: RN2.C2, S6.C, U$2.38
PWM_15: RN2.B2, S7.C, U$2.49
PWM_16: RN2.A2, S8.C, U$2.50
S1: ACTUATORS.5, J1.3, U$2.9
S2: ACTUATORS.6, J2.3, U$2.10
V+: S5.A, S6.A, S7.A, S8.A

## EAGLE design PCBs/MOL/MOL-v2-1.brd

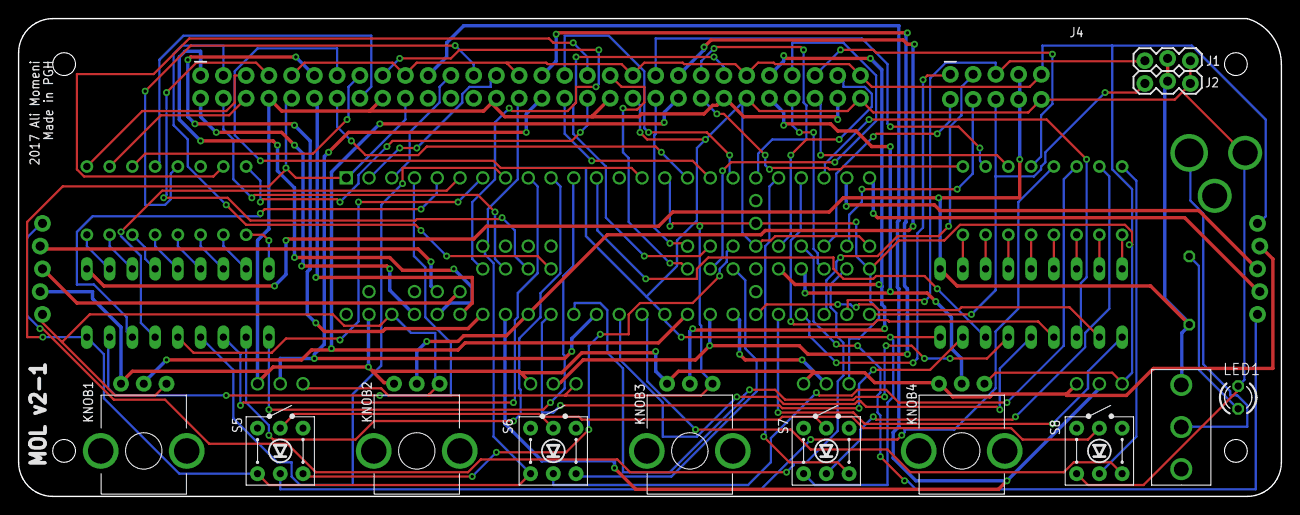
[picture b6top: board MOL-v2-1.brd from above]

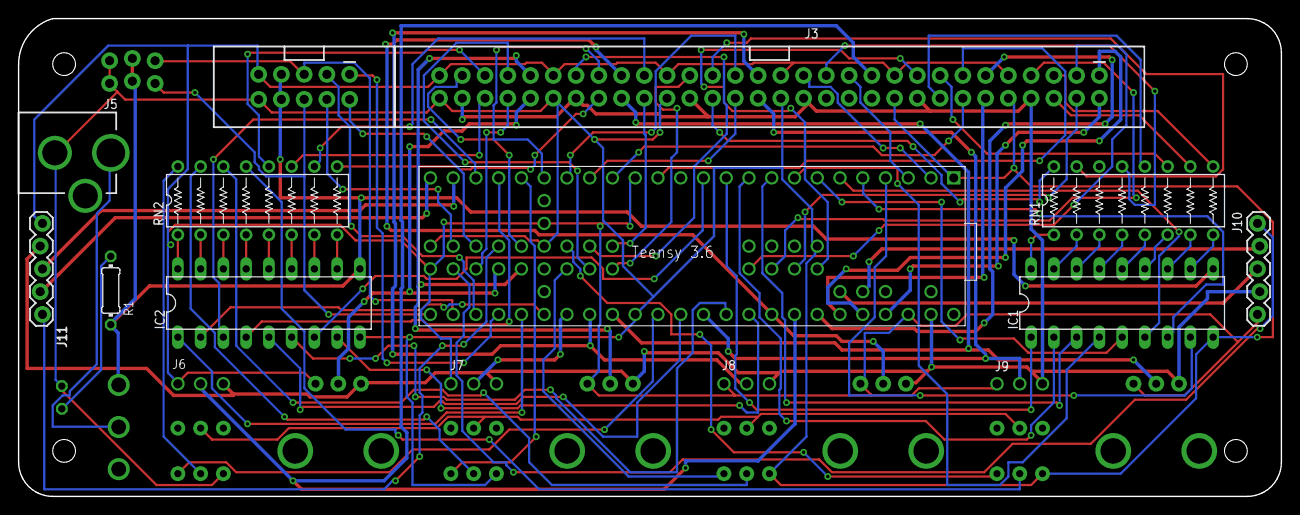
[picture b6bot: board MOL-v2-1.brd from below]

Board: 2 copper layers, 141.0 x 53.3 mm, 27 parts (15 on the bottom side), 99 nets.

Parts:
IC1, IC2: ULN2803; DIL18
J1: SERVO1; 1X03_LOCK@1
J2: SERVO2; 1X03_LOCK@1
J3: STRIPS; 2X30_SHROUDED
J4: ACTUATORS; 2X5-SHROUDED_LOCK
J5: POWER-5V; DCJACK_2MM_PTH
J6: AN-IN-1; 1X03_NO_SILK
J7: AN-IN-2; 1X03_NO_SILK
J8: AN-IN-3; 1X03_NO_SILK
J9: AN-IN-4; 1X03_NO_SILK
J10: JOY1; 1X05_LOCK
J11: JOY2; 1X05_LOCK
KNOB1, KNOB2, KNOB3, KNOB4: TRIM-PCB-9MM
LED1: LED3MM
R1: 330; 0204/7
RN1, RN2: 330; RESISTOR-NET-8P-DIL16
S5, S6, S7, S8: SW-LEDPTH; TR2-SWITCH-MOMENTARY-LED
SW1: 500SSP1S2M2QEA; SWITCH_SPDT_500SSP1S2M2QEA
TEENSY: TEENSY3_6-ALI_NO-USB-HOST; TEENSY3-6_NO-USB-HOST

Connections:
+3V3: J3.9, J3.19, J3.29, J3.39, J3.49, J3.59, J4.9, J6.1, J7.1, J8.1, J9.1, J10.1, J11.1, KNOB1.1, KNOB2.1, KNOB3.1, KNOB4.1, TEENSY.3V3(1), TEENSY.3V3(2), TEENSY.3V3(3), TEENSY.3V3(4)
+5V: IC1.10, IC2.10, J1.2, J2.2, J4.7, J4.8, R1.2, SW1.1
AGND: J3.8, J3.18, J3.28, J3.38, J3.48, J3.58, J6.3, J7.3, J8.3, J9.3, J10.2, J11.2, KNOB1.3, KNOB2.3, KNOB3.3, KNOB4.3, TEENSY.AGND
AN1: J3.1, TEENSY.22
AN2: J3.2, TEENSY.23
AN3: J3.11, TEENSY.20
AN4: J3.12, TEENSY.21
AN5: J3.21, J6.2, TEENSY.19
AN6: J7.2, TEENSY.39
AN7: J3.31, J8.2, TEENSY.DAC0
AN8: J3.32, J9.2, TEENSY.15
AN9: J3.44, KNOB1.2, TEENSY.DAC1
AN10: J3.43, KNOB2.2, TEENSY.18
AN11: J3.51, KNOB3.2, TEENSY.50
AN12: J3.52, KNOB4.2, TEENSY.49
BTN1: J3.3, TEENSY.54
BTN2: J3.4, TEENSY.56
BTN3: J3.13, TEENSY.12
BTN4: J3.14, TEENSY.24
BTN5: J3.23, TEENSY.1
BTN7: J3.33, TEENSY.26
BTN8: J3.34, TEENSY.25
BTN9: J3.45, TEENSY.27
BTN10: J3.42, TEENSY.40
BTN11: J3.53, TEENSY.52
BTN12: J3.54, TEENSY.48
BTN13: S5.1, TEENSY.42
BTN14: S6.1, TEENSY.51
BTN15: S7.1, TEENSY.28
BTN16: S8.1, TEENSY.13
GND: IC1.9, IC2.9, J1.1, J2.1, J3.10, J3.20, J3.30, J3.40, J3.50, J3.60, J4.10, J5.GND, LED1.K, S5.3, S6.3, S7.3, S8.3, TEENSY.G0, TEENSY.G1, TEENSY.G2, TEENSY.G3, TEENSY.G6
JOYB1: J10.5, TEENSY.47
JOYB2: J11.5, TEENSY.44
JOYH1: J10.3, TEENSY.A11
JOYH2: J11.3, TEENSY.31
JOYV1: J10.4, TEENSY.A10
JOYV2: J11.4, TEENSY.32
LED1: J3.7, TEENSY.55
LED2: J3.17, TEENSY.57
LED3: J3.27, TEENSY.0
LED4: J3.37, TEENSY.53
LED5: J3.47, TEENSY.41
LED6: J3.57, TEENSY.43
M_INA: J4.2, TEENSY.45
M_INB: J4.4, TEENSY.46
M_PWMA: J4.1, TEENSY.36
M_PWMB: J4.3, TEENSY.35
unnamed: J5.PWR, SW1.2
unnamed: LED1.A, R1.1
unnamed: IC1.18, RN1.A1
unnamed: IC1.17, RN1.B1
unnamed: IC1.16, RN1.C1
unnamed: IC1.15, RN1.D1
unnamed: IC1.14, RN1.E1
unnamed: IC1.13, RN1.F1
unnamed: IC1.12, RN1.G1
unnamed: IC1.11, RN1.H1
unnamed: IC2.18, RN2.A1
unnamed: IC2.17, RN2.B1
unnamed: IC2.16, RN2.C1
unnamed: IC2.15, RN2.D1
unnamed: IC2.14, RN2.E1
unnamed: IC2.12, RN2.G1
unnamed: IC2.11, RN2.H1
unnamed: IC2.13, RN2.F1
PWM1: IC1.7, TEENSY.3
PWM2: IC1.8, TEENSY.2
PWM3: IC1.5, TEENSY.5
PWM4: IC1.6, TEENSY.4
PWM5: IC1.4, TEENSY.6
PWM6: IC1.3, TEENSY.7
PWM7: IC1.1, TEENSY.9
PWM8: IC1.2, TEENSY.8
PWM9: IC2.7, TEENSY.10
PWM10: IC2.8, TEENSY.17
PWM11: IC2.6, TEENSY.16
PWM12: IC2.5, TEENSY.14
PWM13: IC2.4, TEENSY.29
PWM14: IC2.3, TEENSY.30
PWM15: IC2.2, TEENSY.38
PWM16: IC2.1, TEENSY.37
PWM_1: J3.5, RN1.H2
PWM_2: J3.6, RN1.G2
PWM_3: J3.15, RN1.F2
PWM_4: J3.16, RN1.E2
PWM_5: J3.25, RN1.D2
PWM_7: J3.35, RN1.B2
PWM_8: J3.36, RN1.A2
PWM_9: J3.46, RN2.H2
PWM_10: J3.41, RN2.G2
PWM_11: J3.55, RN2.E2
PWM_12: J3.56, RN2.F2
PWM_13: RN2.D2, S5.C
PWM_14: RN2.C2, S6.C
PWM_15: RN2.B2, S7.C
PWM_16: RN2.A2, S8.C
S1: J1.3, J4.5, TEENSY.34
S2: J2.3, J4.6, TEENSY.33
V+: S5.A, S6.A, S7.A, S8.A

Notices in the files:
parts and their libraries:
SparkFun-Connectors: Licensing: Creative Commons ShareAlike 4.0 International - https://creativecommons.org/licenses/by-sa/4.0
74LV: Copyright (C) 2008, Bob Starr
